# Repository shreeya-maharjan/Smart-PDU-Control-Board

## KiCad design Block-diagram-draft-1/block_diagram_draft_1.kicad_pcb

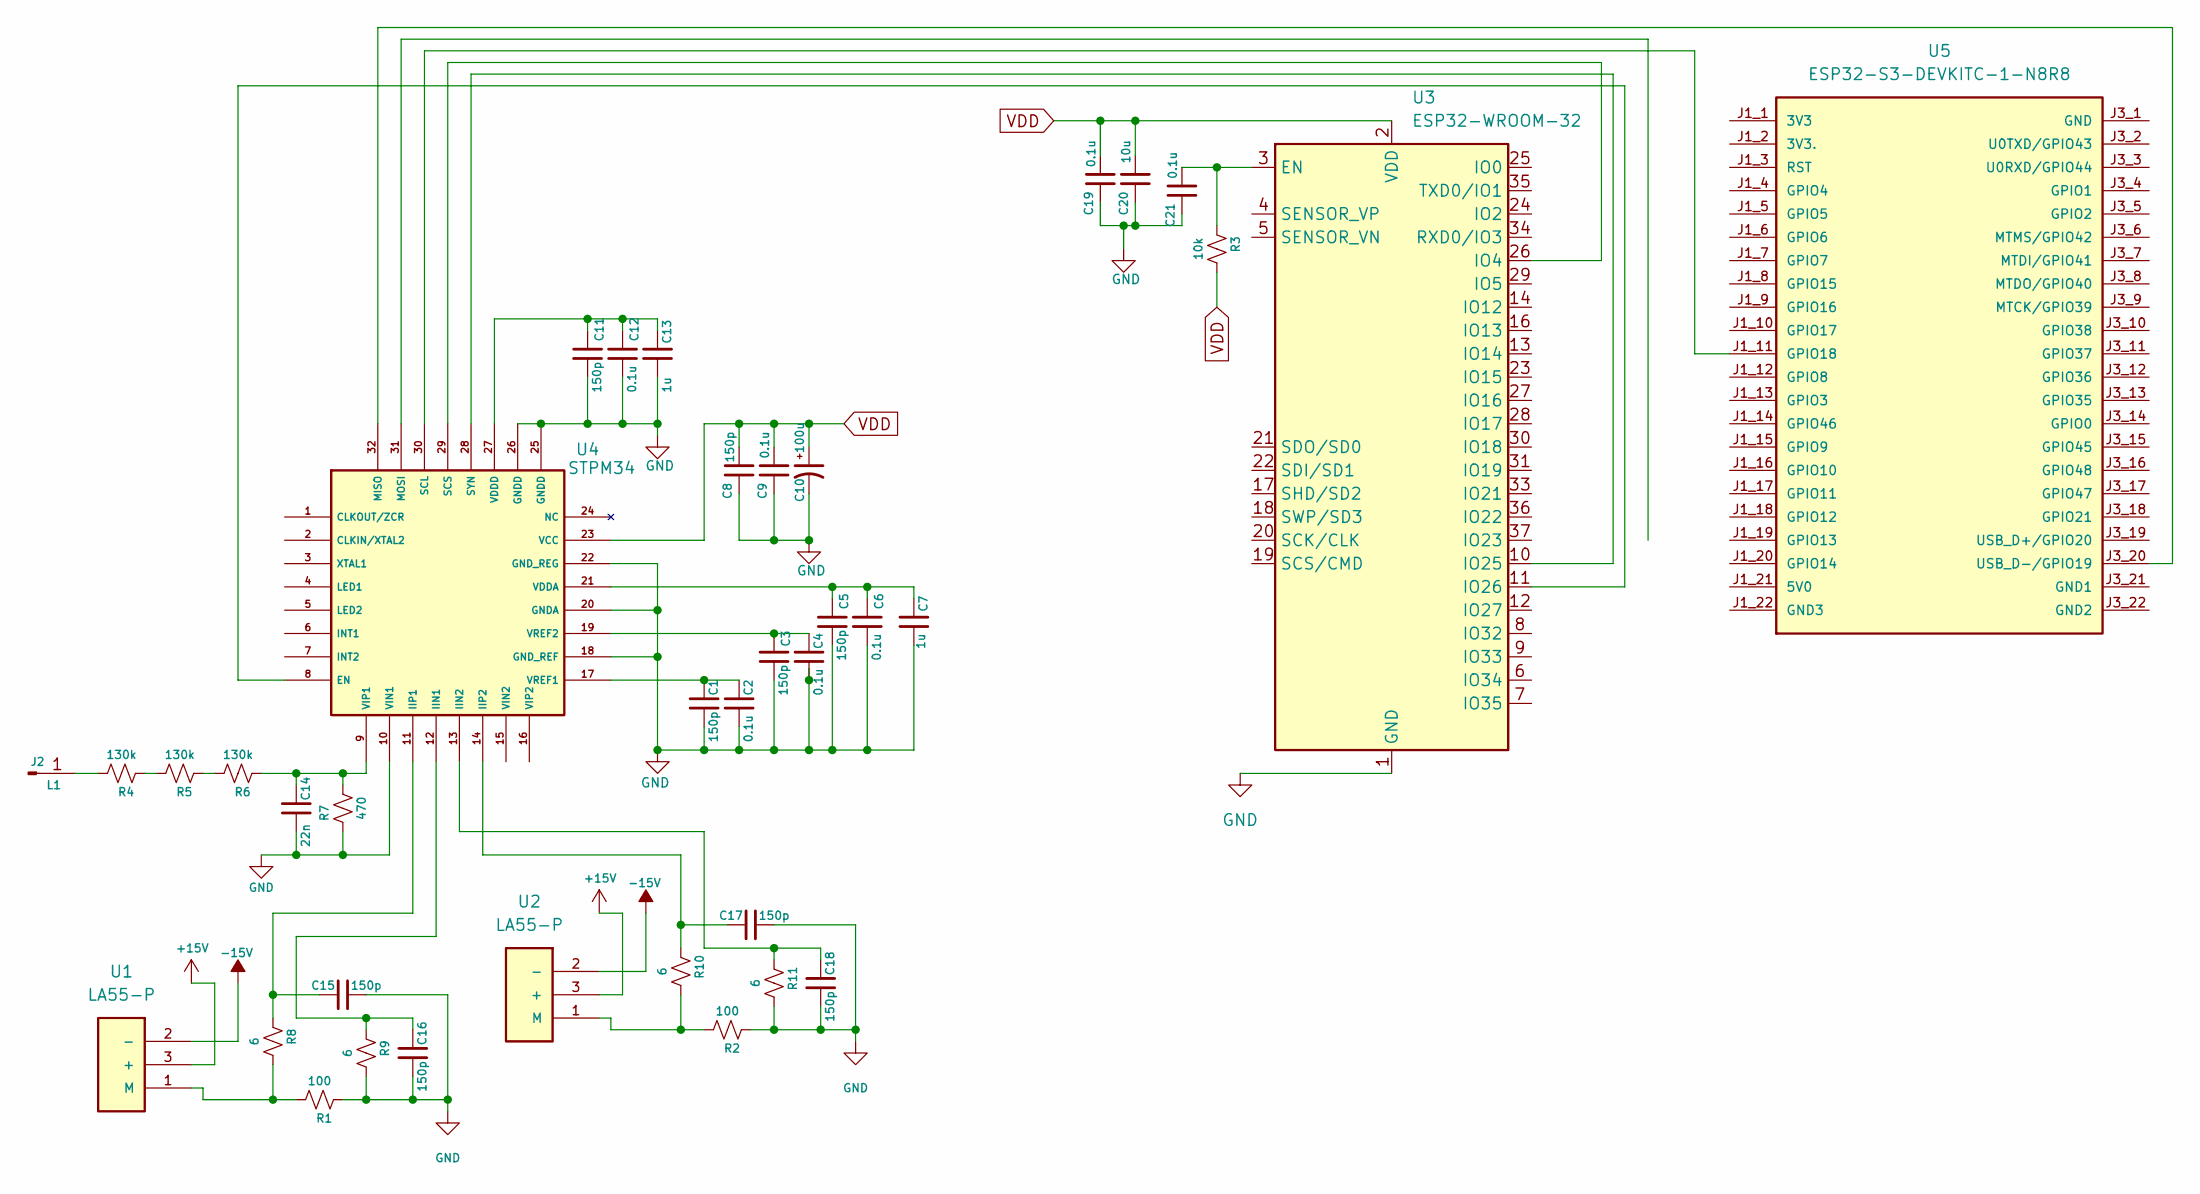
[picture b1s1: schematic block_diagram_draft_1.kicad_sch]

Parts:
C1, C3, C5, C8, C11, C15, C16, C17, C18: 150p; C_0805_2012Metric
C2, C4, C6, C9, C12, C19, C21: 0.1u; C_0805_2012Metric
C7, C13: 1u; C_0805_2012Metric
C10: 100u; CP_Elec_6.3x5.4
C14: 22n; C_0805_2012Metric
C20: 10u; C_0805_2012Metric
J2: L1; PinHeader_1x01_P2.54mm_Vertical
R1, R2: 100; R_0805_2012Metric
R3: 10k; R_0805_2012Metric
R4, R5, R6: 130k; R_1206_3216Metric
R7: 470; R_0805_2012Metric
R8, R9, R10, R11: 6; R_0805_2012Metric
U1, U2: LA55-P; XDCR_LA55-P
U3: ESP32-WROOM-32
U4: STPM34; QFN_PM34_STM
U5: ESP32-S3-DEVKITC-1-N8R8

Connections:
+15V: U1.3 (+), U2.3 (+)
-15V: U1.2 (-), U2.2 (-)
GND: C1.1, C2.1, C3.1, C4.1, C5.1, C6.1, C7.1, C8.2, C9.2, C10.2, C11.1, C12.1, C13.1, C14.1, C15.1, C16.1, C17.1, C18.1, C19.2, C20.2, C21.2, R1.1, R2.1, R7.1, R9.2, R11.2, U3.1 (GND), U3.15 (GND), U3.38 (GND), U3.39 (GND), U4.10 (VIN1), U4.18 (GND_REF), U4.20 (GNDA), U4.22 (GND_REG), U4.25 (GNDD), U4.26 (GNDD)
unnamed: J2.1 (Pin_1_1), R4.2
unnamed: R4.1, R5.2
unnamed: R5.1, R6.2
unnamed: R1.2, R8.2, U1.1 (M)
unnamed: R2.2, R10.2, U2.1 (M)
unnamed: C21.1, R3.1, U3.3 (EN)
unnamed: U3.26 (IO4), U4.29 (SCS)
unnamed: U3.30 (IO18), U4.30 (SCL), U5.J1_11 (GPIO18)
unnamed: U3.31 (IO19), U4.32 (MISO), U5.J3_20 (USB_D-/GPIO19)
unnamed: U3.37 (IO23), U4.31 (MOSI)
unnamed: U3.10 (IO25), U4.28 (SYN)
unnamed: U3.11 (IO26), U4.8 (EN)
unnamed: C16.2, R9.1, U4.12 (IIN1)
unnamed: C18.2, R11.1, U4.13 (IIN2)
unnamed: C15.2, R8.1, U4.11 (IIP1)
unnamed: C17.2, R10.1, U4.14 (IIP2)
unnamed: C5.2, C6.2, C7.2, U4.21 (VDDA)
unnamed: C11.2, C12.2, C13.2, U4.27 (VDDD)
unnamed: C14.2, R6.1, R7.2, U4.9 (VIP1)
unnamed: C1.2, C2.2, U4.17 (VREF1)
unnamed: C3.2, C4.2, U4.19 (VREF2)
VDD: C8.1, C9.1, C10.1, C19.1, C20.1, R3.2, U3.2 (VDD), U4.23 (VCC)

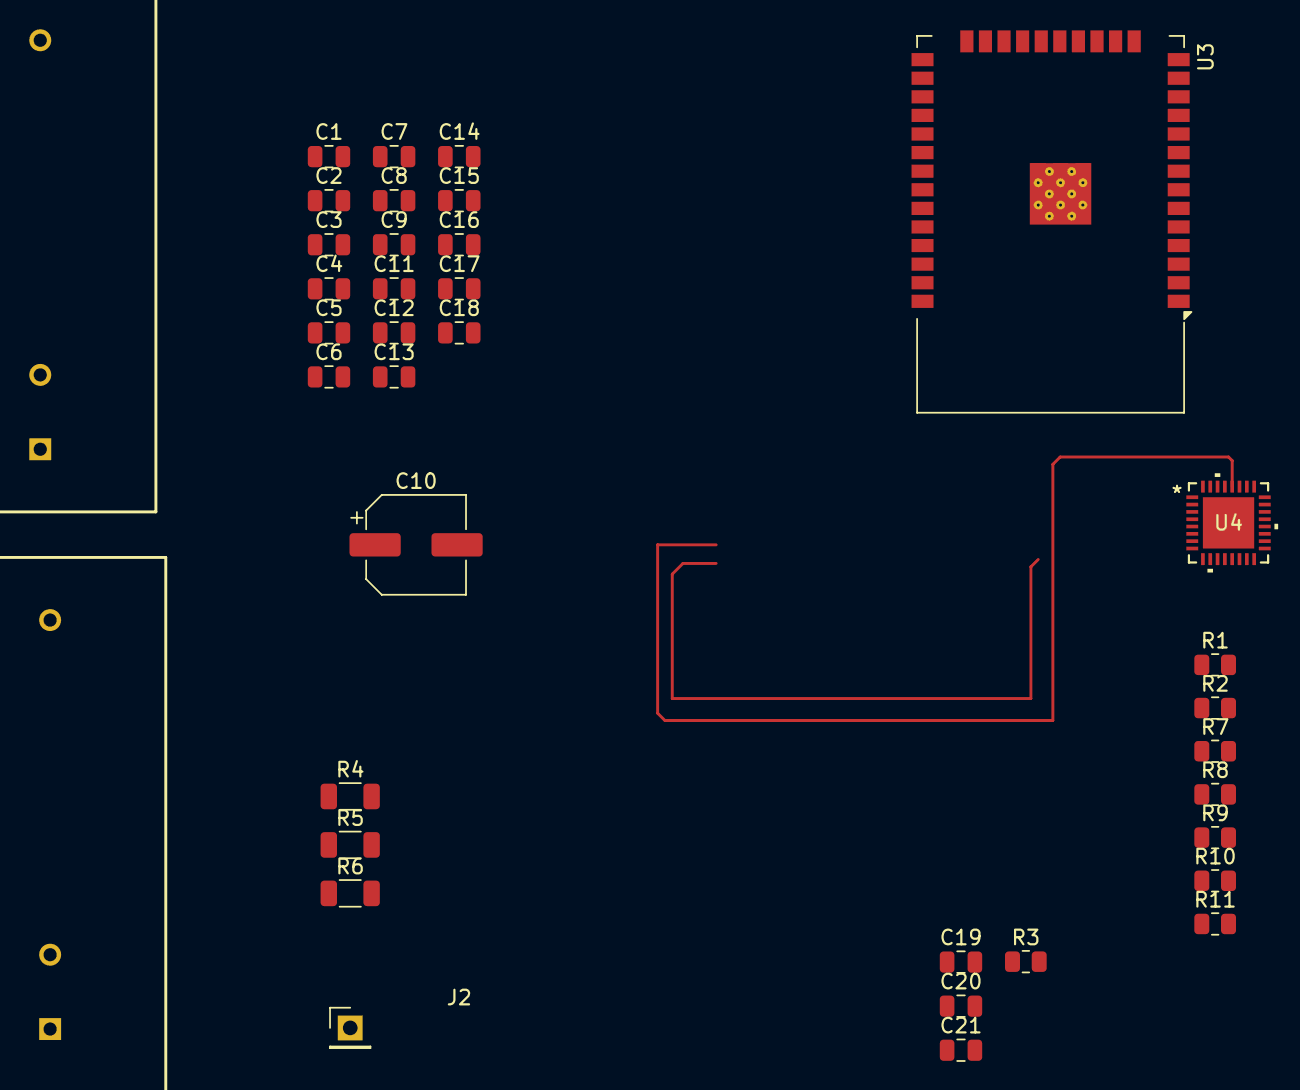
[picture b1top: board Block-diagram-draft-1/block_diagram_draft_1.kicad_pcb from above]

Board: 2 copper layers, 37 parts (0 on the bottom side), 25 nets.

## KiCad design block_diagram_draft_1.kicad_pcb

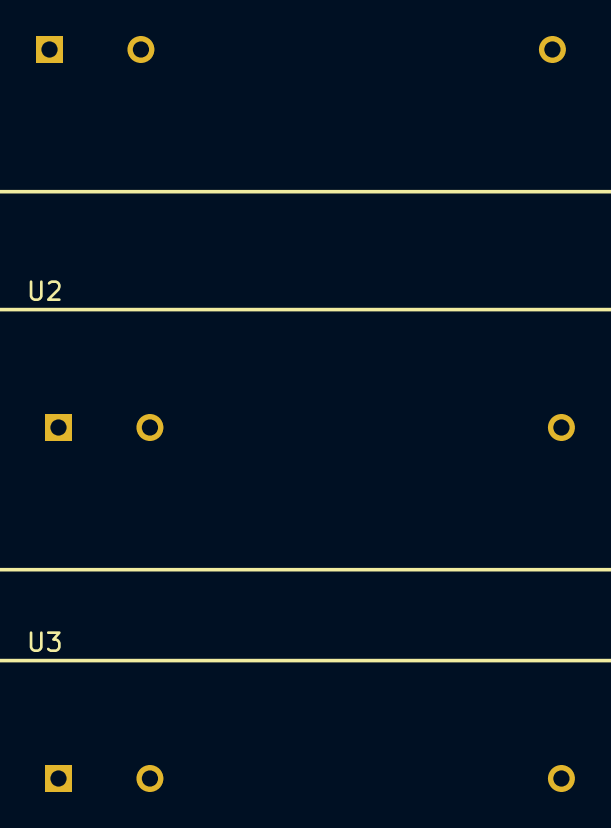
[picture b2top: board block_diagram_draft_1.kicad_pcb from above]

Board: 2 copper layers, 3 parts (0 on the bottom side), 2 nets, no tracks yet.

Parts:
U1, U2, U3: LA55-P; XDCR_LA55-P

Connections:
+15V: U1.3 (+), U2.3 (+), U3.3 (+)
-15V: U1.2 (-), U2.2 (-), U3.2 (-)
